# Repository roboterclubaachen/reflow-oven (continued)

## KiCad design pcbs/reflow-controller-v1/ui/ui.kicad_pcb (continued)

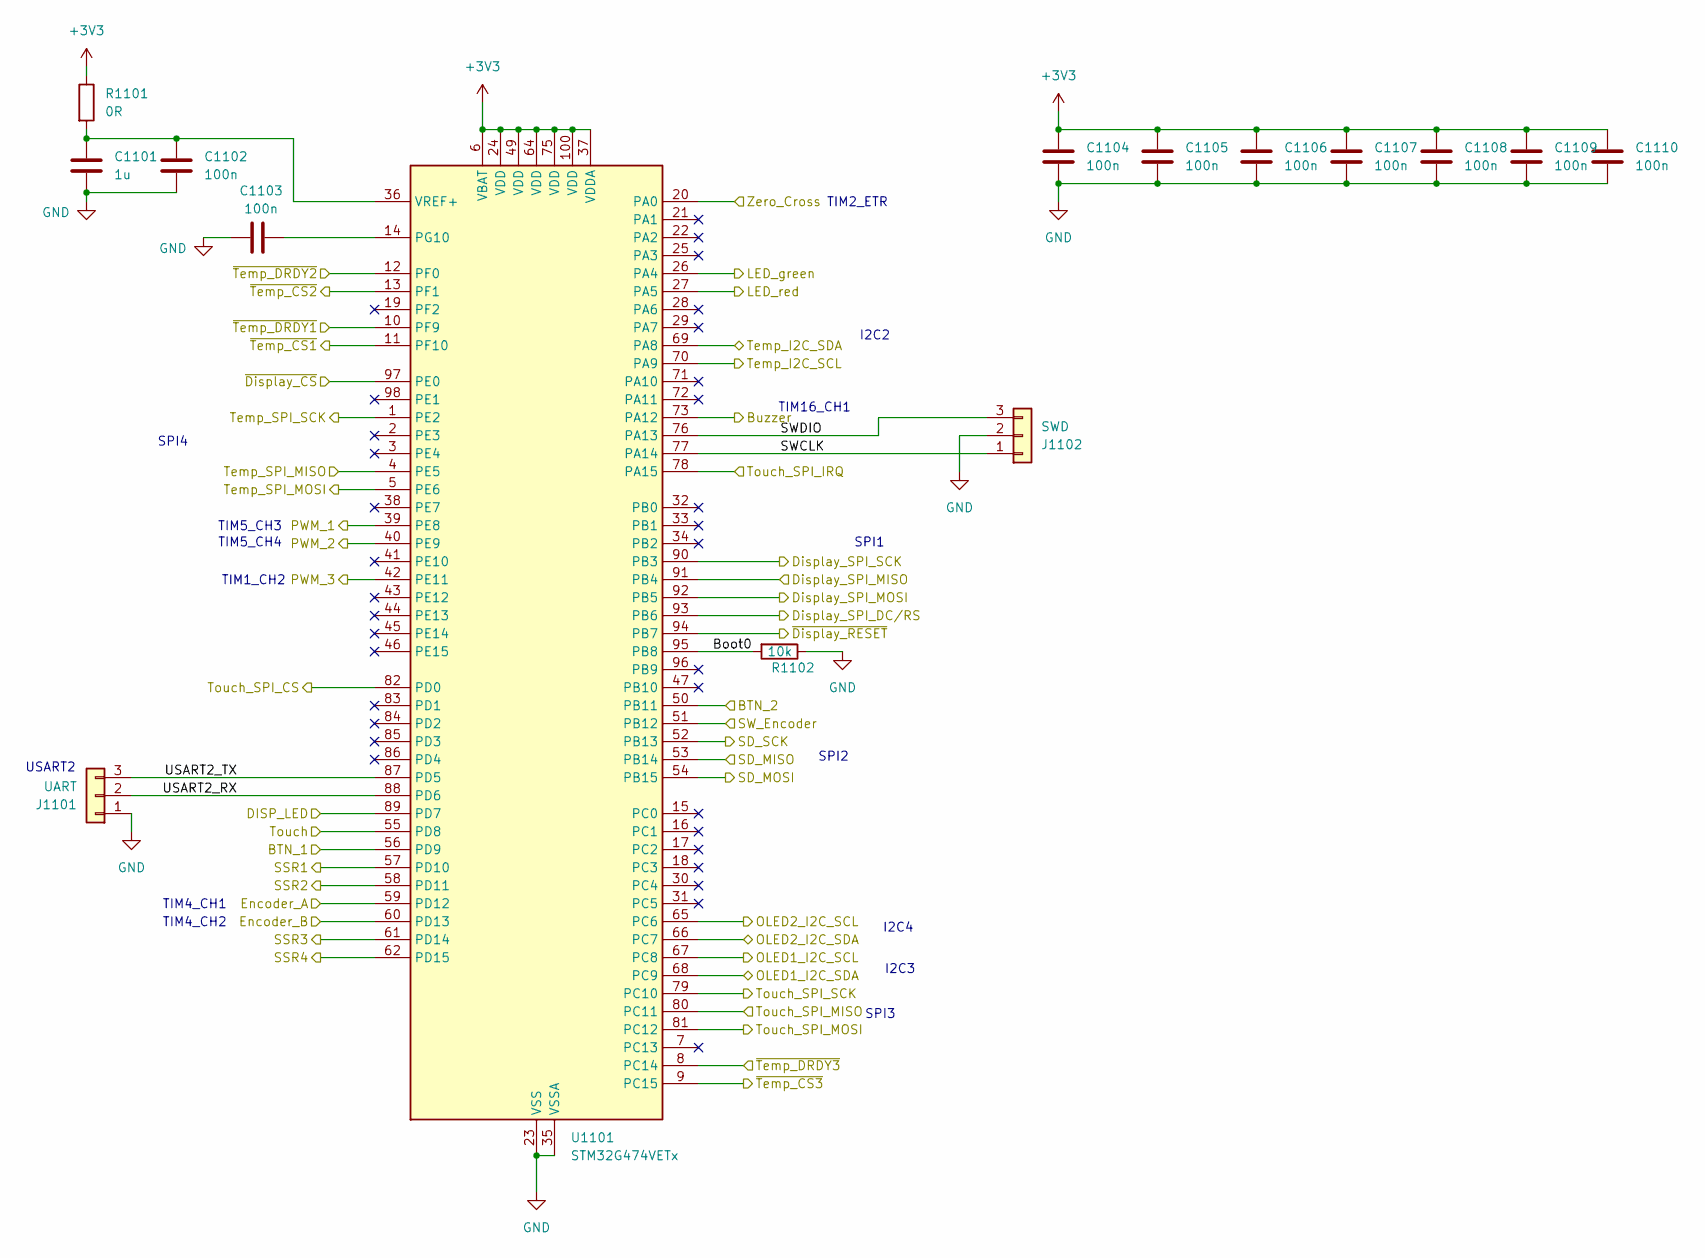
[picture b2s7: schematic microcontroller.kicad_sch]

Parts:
C1101: 1u; C_0603_1608Metric
C1102, C1103, C1104, C1105, C1106, C1107, C1108, C1109, C1110: 100n; C_0603_1608Metric
J1101: UART; Molex_KK-254_AE-6410-03A_1x03_P2.54mm_Vertical
J1102: SWD; Molex_KK-254_AE-6410-03A_1x03_P2.54mm_Vertical
R1101: 0R; R_0603_1608Metric
R1102: 10k; R_0603_1608Metric
U1101: STM32G474VETx; LQFP-100_14x14mm_P0.5mm

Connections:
+3V3: C1104.1, C1105.1, C1106.1, C1107.1, C1108.1, C1109.1, C1110.1, R1101.1, U1101.6 (VBAT), U1101.24 (VDD), U1101.37 (VDDA), U1101.49 (VDD), U1101.64 (VDD), U1101.75 (VDD), U1101.100 (VDD); also elsewhere on the board
/Buttons/Buzzer: U1101.73 (PA12); also elsewhere on the board
/Buttons/Encoder_A: U1101.59 (PD12); also elsewhere on the board
/Buttons/Encoder_B: U1101.60 (PD13); also elsewhere on the board
/Buttons/LED_green: U1101.26 (PA4); also elsewhere on the board
/Buttons/LED_red: U1101.27 (PA5); also elsewhere on the board
/Buttons/SW_1: U1101.56 (PD9); also elsewhere on the board
/Buttons/SW_2: U1101.50 (PB11); also elsewhere on the board
/Buttons/SW_Encoder: U1101.51 (PB12); also elsewhere on the board
/Display LCD/DC/RS: U1101.93 (PB6); also elsewhere on the board
/Display LCD/LED: U1101.89 (PD7); also elsewhere on the board
/Display LCD/MISO: U1101.91 (PB4); also elsewhere on the board
/Display LCD/MOSI: U1101.92 (PB5); also elsewhere on the board
/Display LCD/SCK: U1101.90 (PB3); also elsewhere on the board
/Display LCD/SD_MISO: U1101.53 (PB14); also elsewhere on the board
/Display LCD/SD_MOSI: U1101.54 (PB15); also elsewhere on the board
/Display LCD/SD_SCK: U1101.52 (PB13); also elsewhere on the board
/Display LCD/T_CLK: U1101.79 (PC10); also elsewhere on the board
/Display LCD/T_CS: U1101.82 (PD0); also elsewhere on the board
/Display LCD/T_DIN: U1101.81 (PC12); also elsewhere on the board
/Display LCD/T_DO: U1101.80 (PC11); also elsewhere on the board
/Display LCD/T_IRQ: U1101.78 (PA15); also elsewhere on the board
/Display LCD/Touch: U1101.55 (PD8); also elsewhere on the board
/Display LCD/~CS: U1101.97 (PE0); also elsewhere on the board
/Display LCD/~RESET: U1101.94 (PB7); also elsewhere on the board
/Display OLED 1/I2C_SCL: U1101.67 (PC8); also elsewhere on the board
/Display OLED 1/I2C_SDA: U1101.68 (PC9); also elsewhere on the board
/Display OLED 2/I2C_SCL: U1101.65 (PC6); also elsewhere on the board
/Display OLED 2/I2C_SDA: U1101.66 (PC7); also elsewhere on the board
/Fan_PWM: U1101.42 (PE11); also elsewhere on the board
/PCB Interconnect/SSR1: U1101.57 (PD10); also elsewhere on the board
/PCB Interconnect/SSR2: U1101.58 (PD11); also elsewhere on the board
/PCB Interconnect/SSR3: U1101.62 (PD15); also elsewhere on the board
/PCB Interconnect/SSR4: U1101.61 (PD14); also elsewhere on the board
/PCB Interconnect/Zero: U1101.20 (PA0); also elsewhere on the board
/Servo1: U1101.39 (PE8); also elsewhere on the board
/Servo2: U1101.40 (PE9); also elsewhere on the board
/Temperature onboard 1/SCL: U1101.70 (PA9); also elsewhere on the board
/Temperature onboard 1/SDA: U1101.69 (PA8); also elsewhere on the board
/Temperature sensor 1/SCLK: U1101.1 (PE2); also elsewhere on the board
/Temperature sensor 1/SDI: U1101.5 (PE6); also elsewhere on the board
/Temperature sensor 1/SDO: U1101.4 (PE5); also elsewhere on the board
/Temperature sensor 1/~CS: U1101.9 (PC15); also elsewhere on the board
/Temperature sensor 1/~DRDY: U1101.8 (PC14); also elsewhere on the board
/Temperature sensor 2/~CS: U1101.11 (PF10); also elsewhere on the board
/Temperature sensor 2/~DRDY: U1101.10 (PF9); also elsewhere on the board
/Temperature sensor 3/~CS: U1101.13 (PF1); also elsewhere on the board
/Temperature sensor 3/~DRDY: U1101.12 (PF0); also elsewhere on the board
/microcontroller/Boot0: R1102.2, U1101.95 (PB8)
/microcontroller/SWCLK: J1102.1, U1101.77 (PA14)
/microcontroller/SWDIO: J1102.3, U1101.76 (PA13)
/microcontroller/USART2_RX: J1101.2, U1101.88 (PD6)
/microcontroller/USART2_TX: J1101.3, U1101.87 (PD5)
unnamed: C1103.2, U1101.14 (PG10)
unnamed: C1101.1, C1102.1, R1101.2, U1101.36 (VREF+)

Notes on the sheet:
SPI4
TIM2_ETR
TIM5_CH3
TIM4_CH2
SPI3
I2C4
I2C2
SPI2
TIM16_CH1
TIM4_CH1
SPI1
I2C3
USART2
TIM5_CH4
TIM1_CH2

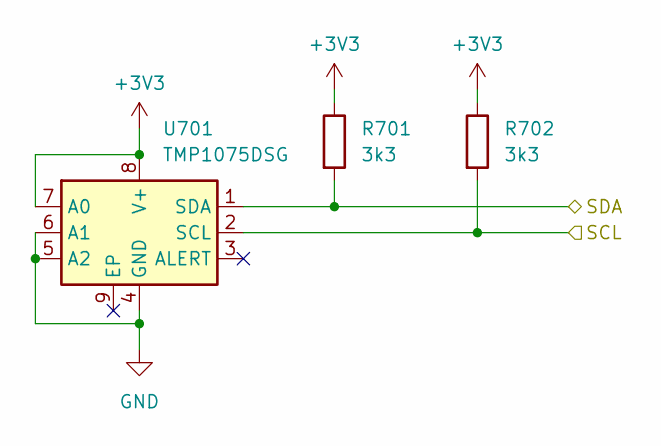
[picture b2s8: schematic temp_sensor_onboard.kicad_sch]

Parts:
R701, R702: 3k3; R_0603_1608Metric
U701: TMP1075DSG; WSON-8-1EP_2x2mm_P0.5mm_EP0.9x1.6mm_ThermalVias

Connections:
+3V3: R701.1, R702.1, U701.7 (A0), U701.8 (V+); also elsewhere on the board
/Temperature onboard 1/SCL: R702.2, U701.2 (SCL); also elsewhere on the board
/Temperature onboard 1/SDA: R701.2, U701.1 (SDA); also elsewhere on the board

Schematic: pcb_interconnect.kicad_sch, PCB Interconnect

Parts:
J801: Power; JST_XH_B3B-XH-A_1x03_P2.50mm_Vertical
J802: Data; JST_GH_BM05B-GHS-TBT_1x05-1MP_P1.25mm_Vertical

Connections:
/Temperature sensor 1/FORCE+: J801.1; also elsewhere on the board
/Temperature sensor 1/RTDIN+: J801.2; also elsewhere on the board

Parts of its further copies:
J201: Power; JST_XH_B3B-XH-A_1x03_P2.50mm_Vertical
J202: Data; JST_GH_BM05B-GHS-TBT_1x05-1MP_P1.25mm_Vertical

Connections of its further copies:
+3.3V: J201.2
+5V: J201.1; also elsewhere on the board
/PCB Interconnect/SSR1: J202.1; also elsewhere on the board
/PCB Interconnect/SSR2: J202.2; also elsewhere on the board
/PCB Interconnect/SSR3: J202.3; also elsewhere on the board
/PCB Interconnect/SSR4: J202.4; also elsewhere on the board
/PCB Interconnect/Zero: J202.5; also elsewhere on the board

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
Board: 2 copper layers, 92 parts (0 on the bottom side), 92 nets, no tracks yet.

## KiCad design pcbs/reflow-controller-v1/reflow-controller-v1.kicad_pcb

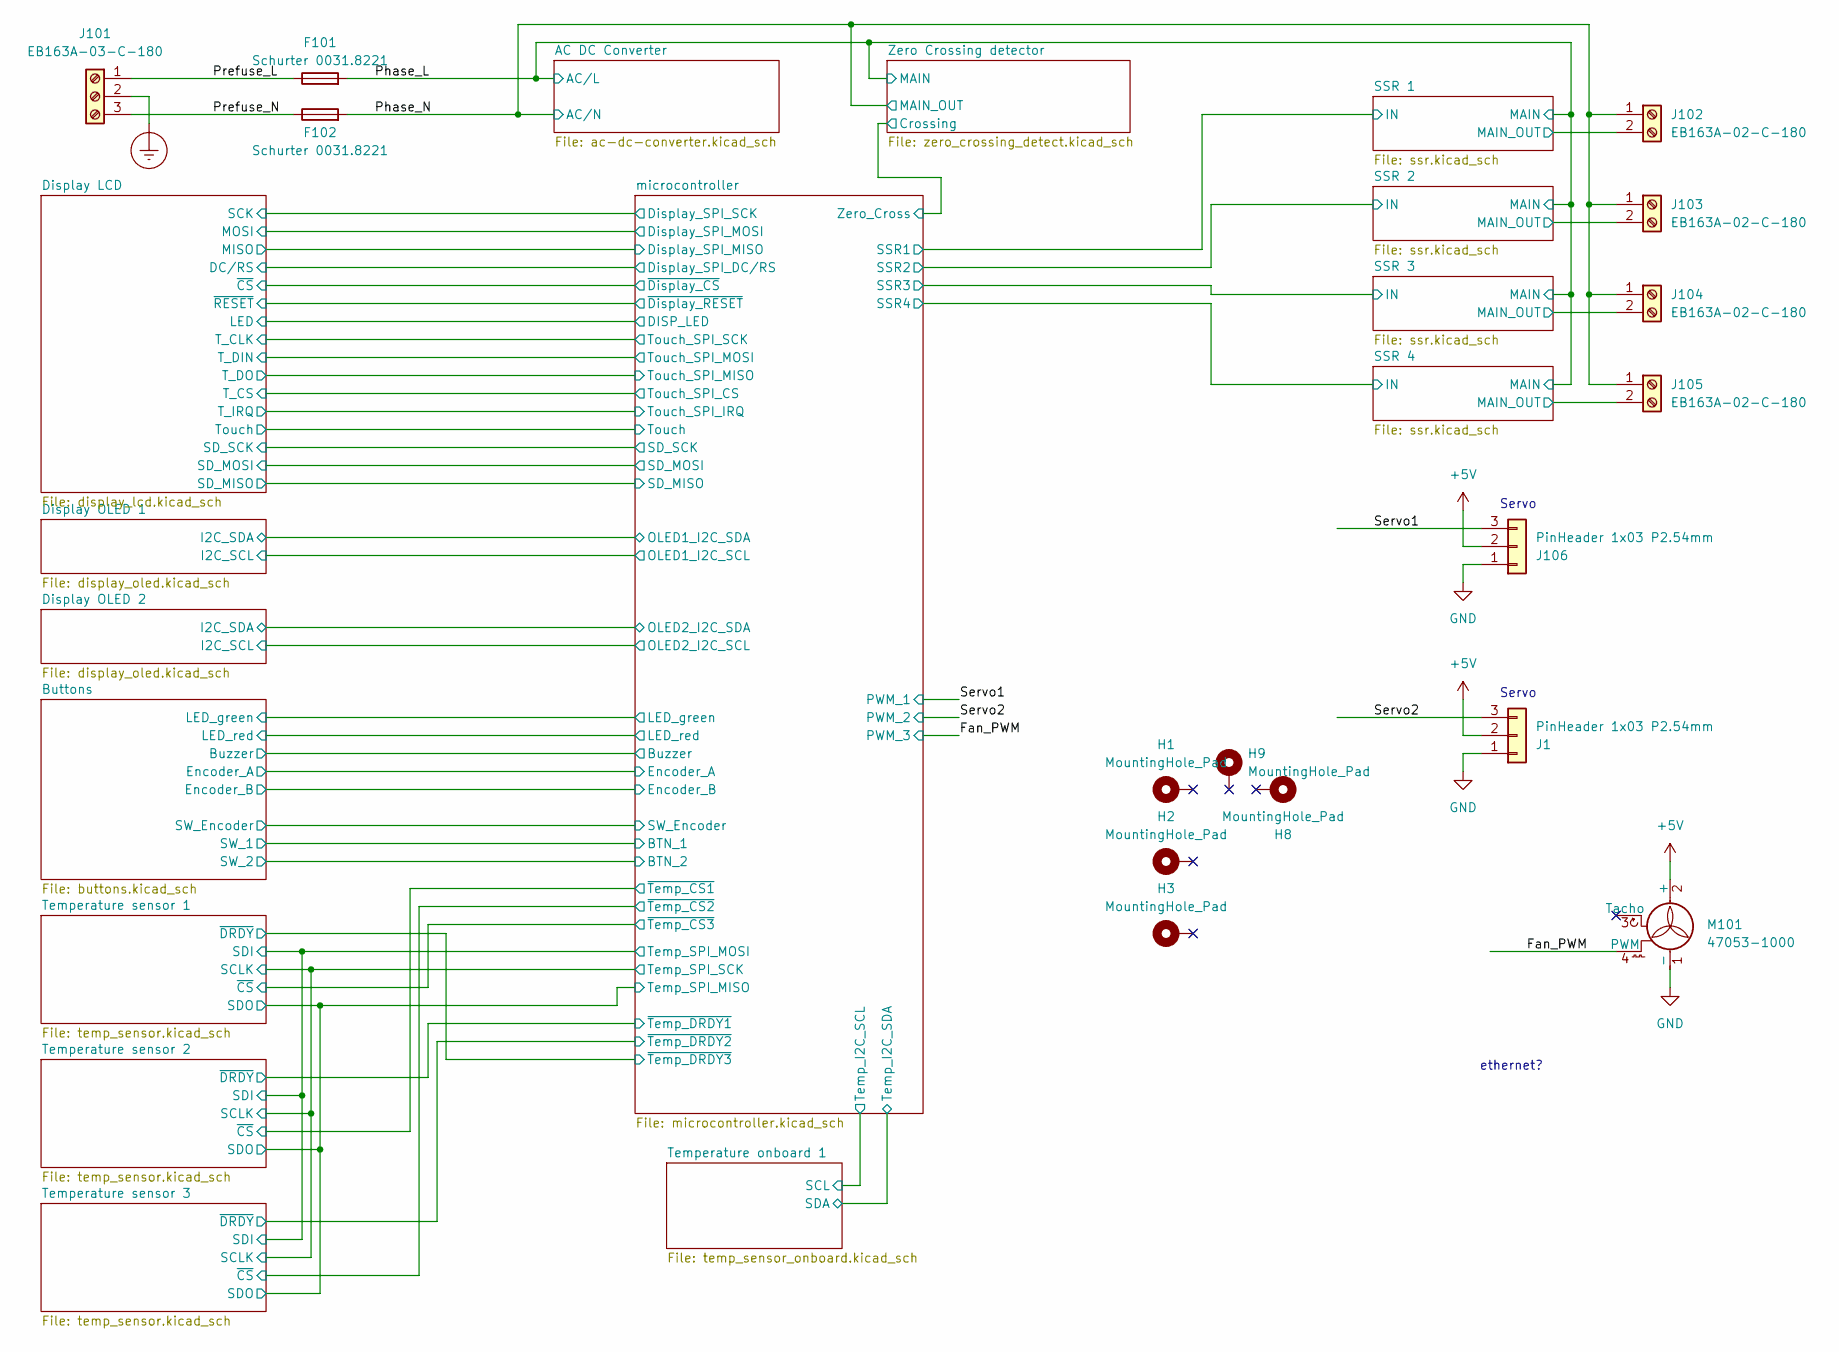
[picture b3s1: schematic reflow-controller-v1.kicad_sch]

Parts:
F101, F102: Schurter 0031.8221; Fuseholder_Cylinder-5x20mm_Schurter_OGN-SMD_Horizontal_Open
H1, H2, H3, H8, H9: MountingHole_Pad; Mounting_Wuerth_WA-SMSI-M3_H15mm_9774150360
J1, J106: PinHeader 1x03 P2.54mm; PinHeader_1x03_P2.54mm_Vertical
J101: EB163A-03-C-180; PhoenixContact_SPT_2.5_3-V-5.0-EX_1x03_P5.0mm_Vertical
J102, J103, J104, J105: EB163A-02-C-180; PhoenixContact_SPT_2.5_2-V-5.0-EX_1x02_P5.0mm_Vertical
M101: 47053-1000; Molex_KK-254_AE-6410-04A_1x04_P2.54mm_Vertical

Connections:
+5V: J1.2, J106.2, M101.2 (+); also elsewhere on the board
/Fan_PWM: M101.4 (PWM); also elsewhere on the board
/Phase_L: F101.2; also elsewhere on the board
/Phase_N: F102.2, J102.1, J103.1, J104.1, J105.1; also elsewhere on the board
/Prefuse_L: F101.1, J101.1
/Prefuse_N: F102.1, J101.3
/SSR 1/MAIN_OUT: J102.2; also elsewhere on the board
/SSR 2/MAIN_OUT: J103.2; also elsewhere on the board
/SSR 3/MAIN_OUT: J104.2; also elsewhere on the board
/SSR 4/MAIN_OUT: J105.2; also elsewhere on the board
/Servo1: J106.3; also elsewhere on the board
/Servo2: J1.3; also elsewhere on the board
Earth_Protective: J101.2
GND: J1.1, J106.1, M101.1 (-); also elsewhere on the board

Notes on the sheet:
Servo
ethernet?

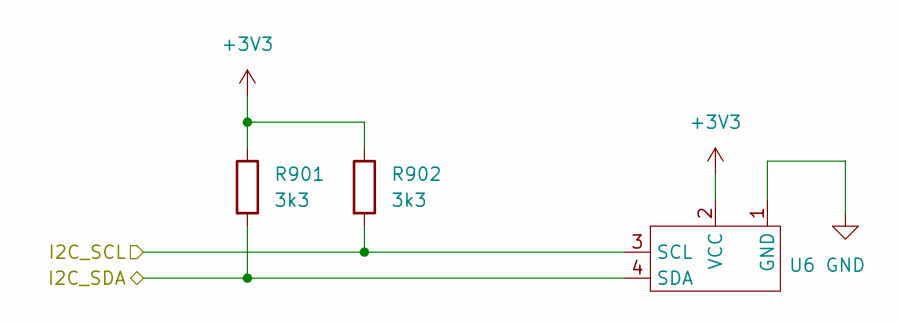
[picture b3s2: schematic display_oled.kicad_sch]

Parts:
R901, R902: 3k3; R_0603_1608Metric
U6: SSD1315 Module

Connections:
+3V3: R901.1, R902.1, U6.2 (VCC); also elsewhere on the board
/Display OLED 2/I2C_SCL: R902.2, U6.3 (SCL); also elsewhere on the board
/Display OLED 2/I2C_SDA: R901.2, U6.4 (SDA); also elsewhere on the board
GND: U6.1 (GND); also elsewhere on the board

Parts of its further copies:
R801, R802: 3k3; R_0603_1608Metric
U5: SSD1315 Module

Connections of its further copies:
+3V3: R801.1, R802.1, U5.2 (VCC); also elsewhere on the board
/Display OLED 1/I2C_SCL: R802.2, U5.3 (SCL); also elsewhere on the board
/Display OLED 1/I2C_SDA: R801.2, U5.4 (SDA); also elsewhere on the board
GND: U5.1 (GND); also elsewhere on the board

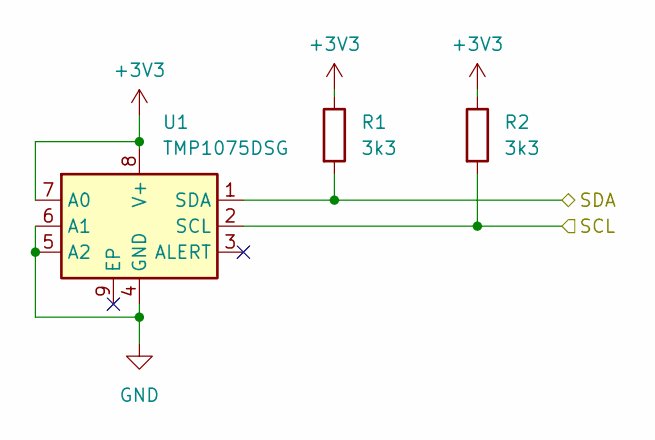
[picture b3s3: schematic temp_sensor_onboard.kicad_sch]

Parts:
R1, R2: 3k3; R_0603_1608Metric
U1: TMP1075DSG; WSON-8-1EP_2x2mm_P0.5mm_EP0.9x1.6mm_ThermalVias

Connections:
+3V3: R1.1, R2.1, U1.7 (A0), U1.8 (V+); also elsewhere on the board
/Temperature onboard 1/SCL: R2.2, U1.2 (SCL); also elsewhere on the board
/Temperature onboard 1/SDA: R1.2, U1.1 (SDA); also elsewhere on the board
GND: U1.4 (GND), U1.5 (A2), U1.6 (A1); also elsewhere on the board

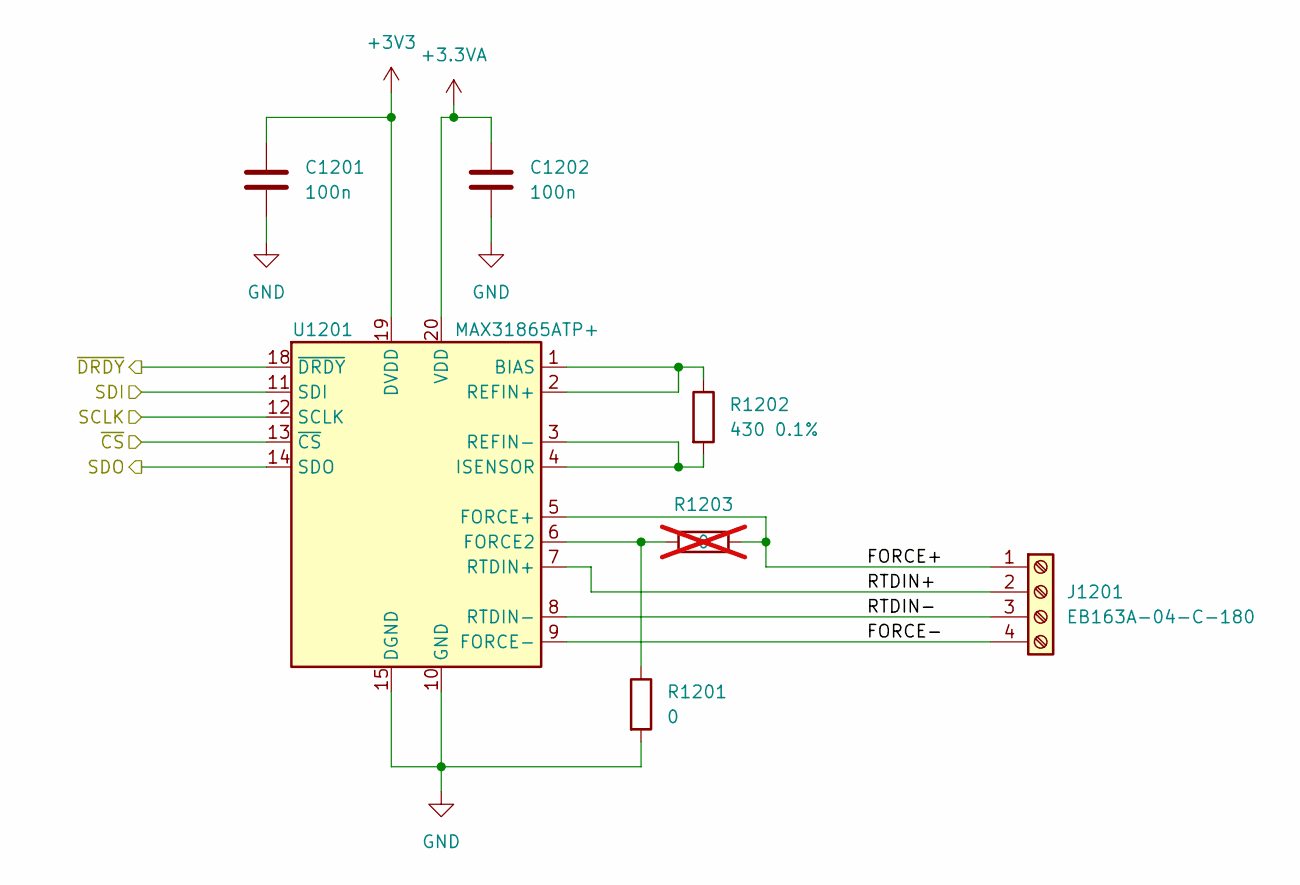
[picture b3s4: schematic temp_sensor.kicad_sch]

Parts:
C1201, C1202: 100n; C_0603_1608Metric
J1201: EB163A-04-C-180; PhoenixContact_SPT_2.5_4-V-5.0-EX_1x04_P5.0mm_Vertical
R1201: 0; R_0603_1608Metric
R1202: 430 0.1%; R_1206_3216Metric
R1203: 0; R_0603_1608Metric; not fitted
U1201: MAX31865ATP+; TQFN-20-1EP_5x5mm_P0.65mm_EP3.25x3.25mm

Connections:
+3.3VA: C1202.1, U1201.20 (VDD); also elsewhere on the board
+3V3: C1201.1, U1201.19 (DVDD); also elsewhere on the board
/Temperature sensor 1/SCLK: U1201.12 (SCLK); also elsewhere on the board
/Temperature sensor 1/SDI: U1201.11 (SDI); also elsewhere on the board
/Temperature sensor 1/SDO: U1201.14 (SDO); also elsewhere on the board
/Temperature sensor 2/FORCE+: J1201.1, R1203.2, U1201.5 (FORCE+)
/Temperature sensor 2/FORCE-: J1201.4, U1201.9 (FORCE-)
/Temperature sensor 2/RTDIN+: J1201.2, U1201.7 (RTDIN+)
/Temperature sensor 2/RTDIN-: J1201.3, U1201.8 (RTDIN-)
/Temperature sensor 2/~CS: U1201.13 (~CS); also elsewhere on the board
/Temperature sensor 2/~DRDY: U1201.18 (~DRDY); also elsewhere on the board
GND: C1201.2, C1202.2, R1201.2, U1201.10 (GND), U1201.15 (DGND), U1201.16 (GND), U1201.21 (GND); also elsewhere on the board
unnamed: R1202.1, U1201.1 (BIAS), U1201.2 (REFIN+)
unnamed: R1201.1, R1203.1, U1201.6 (FORCE2)
unnamed: R1202.2, U1201.3 (REFIN-), U1201.4 (ISENSOR)

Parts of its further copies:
C1101, C1102, C1301, C1302: 100n; C_0603_1608Metric
J1101, J1301: EB163A-04-C-180; PhoenixContact_SPT_2.5_4-V-5.0-EX_1x04_P5.0mm_Vertical
R1101, R1302: 430 0.1%; R_1206_3216Metric
R1102, R1301: 0; R_0603_1608Metric
R1103, R1303: 0; R_0603_1608Metric; not fitted
U1101, U1301: MAX31865ATP+; TQFN-20-1EP_5x5mm_P0.65mm_EP3.25x3.25mm

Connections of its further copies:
+3.3VA: C1101.1, C1302.1, U1101.20 (VDD), U1301.20 (VDD); also elsewhere on the board
+3V3: C1102.1, C1301.1, U1101.19 (DVDD), U1301.19 (DVDD); also elsewhere on the board
/Temperature sensor 1/FORCE+: J1101.1, R1103.2, U1101.5 (FORCE+)
/Temperature sensor 1/FORCE-: J1101.4, U1101.9 (FORCE-)
/Temperature sensor 1/RTDIN+: J1101.2, U1101.7 (RTDIN+)
/Temperature sensor 1/RTDIN-: J1101.3, U1101.8 (RTDIN-)
/Temperature sensor 1/SCLK: U1101.12 (SCLK), U1301.12 (SCLK); also elsewhere on the board
/Temperature sensor 1/SDI: U1101.11 (SDI), U1301.11 (SDI); also elsewhere on the board
/Temperature sensor 1/SDO: U1101.14 (SDO), U1301.14 (SDO); also elsewhere on the board
/Temperature sensor 1/~CS: U1101.13 (~CS); also elsewhere on the board
/Temperature sensor 1/~DRDY: U1101.18 (~DRDY); also elsewhere on the board
/Temperature sensor 3/FORCE+: J1301.1, R1303.2, U1301.5 (FORCE+)
/Temperature sensor 3/FORCE-: J1301.4, U1301.9 (FORCE-)
/Temperature sensor 3/RTDIN+: J1301.2, U1301.7 (RTDIN+)
/Temperature sensor 3/RTDIN-: J1301.3, U1301.8 (RTDIN-)
/Temperature sensor 3/~CS: U1301.13 (~CS); also elsewhere on the board
/Temperature sensor 3/~DRDY: U1301.18 (~DRDY); also elsewhere on the board
GND: C1101.2, C1102.2, C1301.2, C1302.2, R1102.2, R1301.2, U1101.10 (GND), U1101.15 (DGND), U1101.16 (GND), U1101.21 (GND), U1301.10 (GND), U1301.15 (DGND), U1301.16 (GND), U1301.21 (GND); also elsewhere on the board
unnamed: R1101.1, U1101.1 (BIAS), U1101.2 (REFIN+)
unnamed: R1102.1, R1103.1, U1101.6 (FORCE2)
unnamed: R1101.2, U1101.3 (REFIN-), U1101.4 (ISENSOR)
unnamed: R1302.1, U1301.1 (BIAS), U1301.2 (REFIN+)
unnamed: R1301.1, R1303.1, U1301.6 (FORCE2)
unnamed: R1302.2, U1301.3 (REFIN-), U1301.4 (ISENSOR)

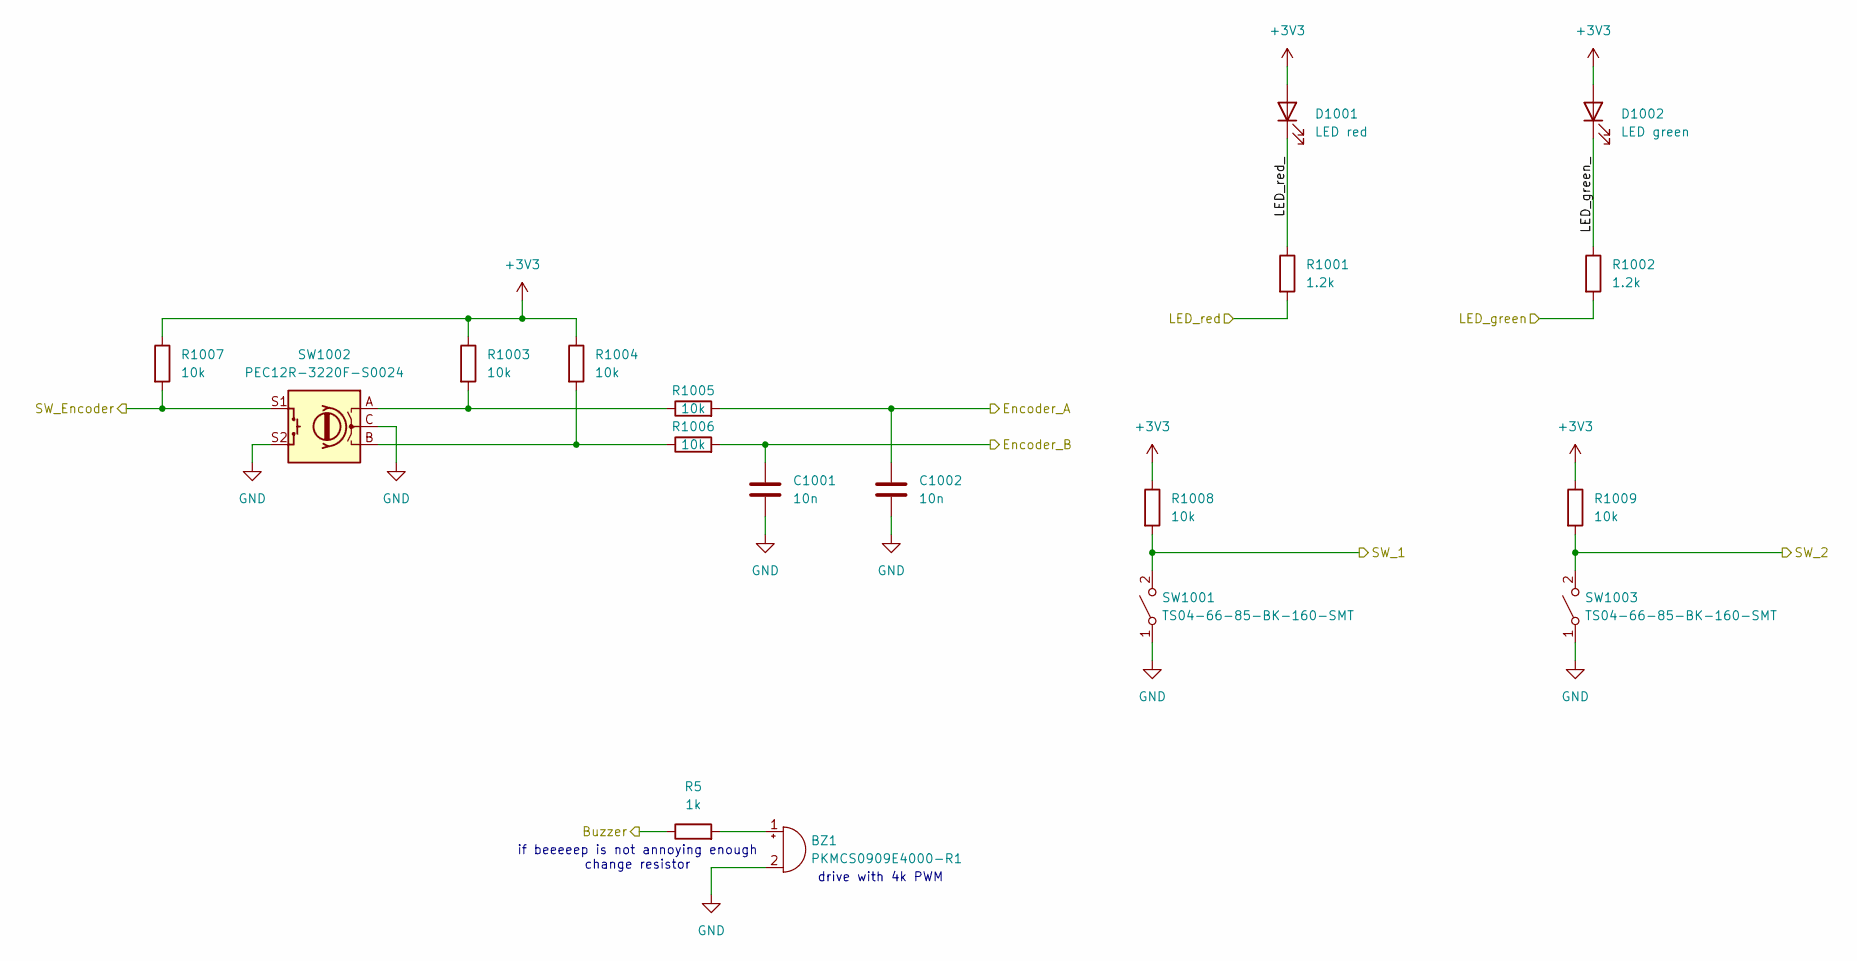
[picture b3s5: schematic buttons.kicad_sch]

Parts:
BZ1: PKMCS0909E4000-R1; Buzzer_Murata_PKMCS0909E
C1001, C1002: 10n; C_0603_1608Metric
D1001: LED red; LED_0603_1608Metric
D1002: LED green; LED_0603_1608Metric
R5: 1k; R_0603_1608Metric
R1001, R1002: 1.2k; R_0603_1608Metric
R1003, R1004, R1005, R1006, R1007, R1008, R1009: 10k; R_0603_1608Metric
SW1001, SW1003: TS04-66-85-BK-160-SMT; SW_Push_1P1T_NO_6x6mm_H9.5mm
SW1002: PEC12R-3220F-S0024; RotaryEncoder_Bourns_Vertical_PEC12R-3x17F-Sxxxx

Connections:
+3V3: D1001.2 (A), D1002.2 (A), R1003.1, R1004.1, R1007.1, R1008.1, R1009.1; also elsewhere on the board
/Buttons/Buzzer: R5.1; also elsewhere on the board
/Buttons/Encoder_A: C1002.1, R1005.2; also elsewhere on the board
/Buttons/Encoder_B: C1001.1, R1006.2; also elsewhere on the board
/Buttons/LED_green: R1002.2; also elsewhere on the board
/Buttons/LED_green_: D1002.1 (K), R1002.1
/Buttons/LED_red: R1001.2; also elsewhere on the board
/Buttons/LED_red_: D1001.1 (K), R1001.1
/Buttons/SW_1: R1008.2, SW1001.2 (B); also elsewhere on the board
/Buttons/SW_2: R1009.2, SW1003.2 (B); also elsewhere on the board
/Buttons/SW_Encoder: R1007.2, SW1002.S1; also elsewhere on the board
GND: BZ1.2 (-), C1001.2, C1002.2, SW1001.1 (A), SW1002.C, SW1002.S2, SW1003.1 (A); also elsewhere on the board
unnamed: BZ1.1 (+), R5.2
unnamed: R1003.2, R1005.1, SW1002.A
unnamed: R1004.2, R1006.1, SW1002.B

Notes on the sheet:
if beeeeep is not annoying enough change resistor
drive with 4k PWM

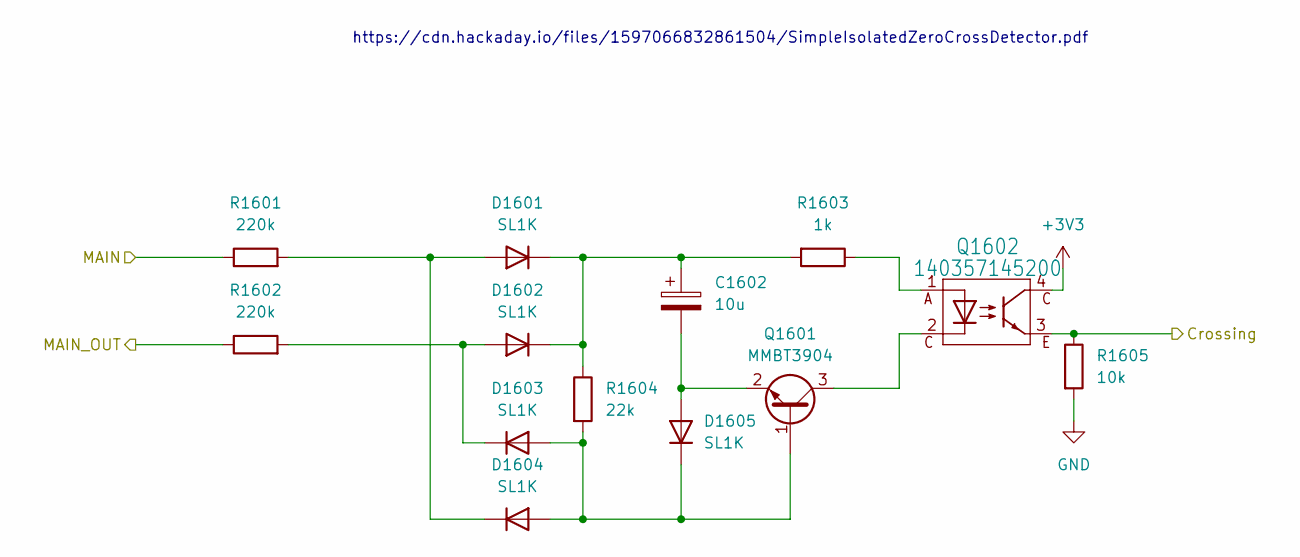
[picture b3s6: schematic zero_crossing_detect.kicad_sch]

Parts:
C1602: 10u; CP_Elec_4x5.7
D1601, D1602, D1603, D1604, D1605: SL1K; D_SOD-123F
Q1601: MMBT3904; SOT-23
Q1602: 140357145200; WL-OCPT_LSOP4
R1601, R1602: 220k; R_1206_3216Metric
R1603: 1k; R_0603_1608Metric
R1604: 22k; R_0603_1608Metric
R1605: 10k; R_0603_1608Metric

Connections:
+3V3: Q1602.4; also elsewhere on the board
/Phase_L: R1601.1; also elsewhere on the board
/Phase_N: R1602.1; also elsewhere on the board
/Zero Crossing detector/Crossing: Q1602.3, R1605.1; also elsewhere on the board
GND: R1605.2; also elsewhere on the board
unnamed: D1601.2 (A), D1604.1 (K), R1601.2
unnamed: C1602.1, D1601.1 (K), D1602.1 (K), R1603.2, R1604.1
unnamed: D1602.2 (A), D1603.1 (K), R1602.2
unnamed: D1603.2 (A), D1604.2 (A), D1605.1 (K), Q1601.1 (B), R1604.2
unnamed: C1602.2, D1605.2 (A), Q1601.2 (E)
unnamed: Q1601.3 (C), Q1602.2
unnamed: Q1602.1, R1603.1

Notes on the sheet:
https://cdn.hackaday.io/files/1597066832861504/SimpleIsolatedZeroCrossDetector.pdf

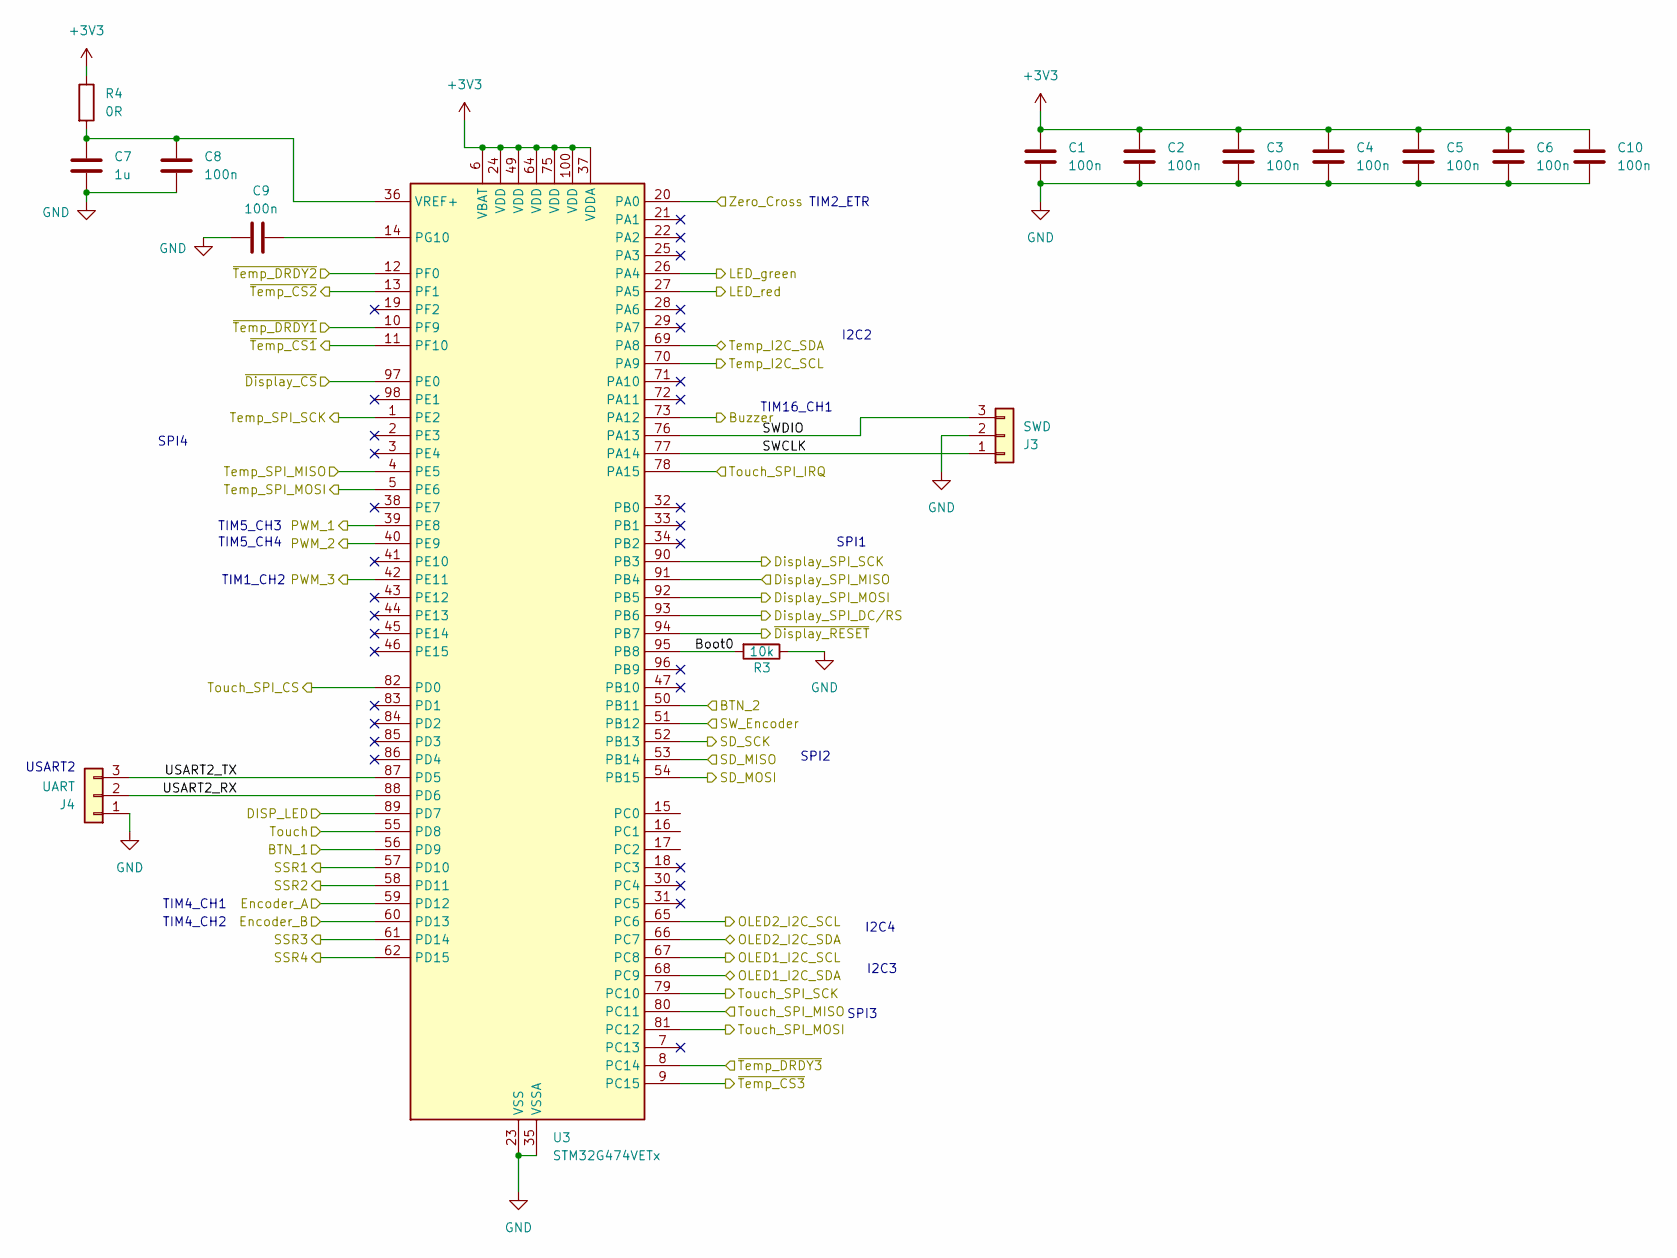
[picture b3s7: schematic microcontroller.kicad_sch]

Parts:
C1, C2, C3, C4, C5, C6, C8, C9, C10: 100n; C_0603_1608Metric
C7: 1u; C_0603_1608Metric
J3: SWD; Molex_KK-254_AE-6410-03A_1x03_P2.54mm_Vertical
J4: UART; Molex_KK-254_AE-6410-03A_1x03_P2.54mm_Vertical
R3: 10k; R_0603_1608Metric
R4: 0R; R_0603_1608Metric
U3: STM32G474VETx; LQFP-100_14x14mm_P0.5mm

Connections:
+3V3: C1.1, C2.1, C3.1, C4.1, C5.1, C6.1, C10.1, R4.1, U3.6 (VBAT), U3.24 (VDD), U3.37 (VDDA), U3.49 (VDD), U3.64 (VDD), U3.75 (VDD), U3.100 (VDD); also elsewhere on the board
/Buttons/Buzzer: U3.73 (PA12); also elsewhere on the board
/Buttons/Encoder_A: U3.59 (PD12); also elsewhere on the board
/Buttons/Encoder_B: U3.60 (PD13); also elsewhere on the board
/Buttons/LED_green: U3.26 (PA4); also elsewhere on the board
/Buttons/LED_red: U3.27 (PA5); also elsewhere on the board
/Buttons/SW_1: U3.56 (PD9); also elsewhere on the board
/Buttons/SW_2: U3.50 (PB11); also elsewhere on the board
/Buttons/SW_Encoder: U3.51 (PB12); also elsewhere on the board
/Display LCD/DC/RS: U3.93 (PB6); also elsewhere on the board
/Display LCD/LED: U3.89 (PD7); also elsewhere on the board
/Display LCD/MISO: U3.91 (PB4); also elsewhere on the board
/Display LCD/MOSI: U3.92 (PB5); also elsewhere on the board
/Display LCD/SCK: U3.90 (PB3); also elsewhere on the board
/Display LCD/SD_MISO: U3.53 (PB14); also elsewhere on the board
/Display LCD/SD_MOSI: U3.54 (PB15); also elsewhere on the board
/Display LCD/SD_SCK: U3.52 (PB13); also elsewhere on the board
/Display LCD/T_CLK: U3.79 (PC10); also elsewhere on the board
/Display LCD/T_CS: U3.82 (PD0); also elsewhere on the board
/Display LCD/T_DIN: U3.81 (PC12); also elsewhere on the board
/Display LCD/T_DO: U3.80 (PC11); also elsewhere on the board
/Display LCD/T_IRQ: U3.78 (PA15); also elsewhere on the board
/Display LCD/Touch: U3.55 (PD8); also elsewhere on the board
/Display LCD/~CS: U3.97 (PE0); also elsewhere on the board
/Display LCD/~RESET: U3.94 (PB7); also elsewhere on the board
/Display OLED 1/I2C_SCL: U3.67 (PC8); also elsewhere on the board
/Display OLED 1/I2C_SDA: U3.68 (PC9); also elsewhere on the board
/Display OLED 2/I2C_SCL: U3.65 (PC6); also elsewhere on the board
/Display OLED 2/I2C_SDA: U3.66 (PC7); also elsewhere on the board
/Fan_PWM: U3.42 (PE11); also elsewhere on the board
/SSR 1/IN: U3.57 (PD10); also elsewhere on the board
/SSR 2/IN: U3.58 (PD11); also elsewhere on the board
/SSR 3/IN: U3.61 (PD14); also elsewhere on the board
/SSR 4/IN: U3.62 (PD15); also elsewhere on the board
/Servo1: U3.39 (PE8); also elsewhere on the board
/Servo2: U3.40 (PE9); also elsewhere on the board
/Temperature onboard 1/SCL: U3.70 (PA9); also elsewhere on the board
/Temperature onboard 1/SDA: U3.69 (PA8); also elsewhere on the board
/Temperature sensor 1/SCLK: U3.1 (PE2); also elsewhere on the board
/Temperature sensor 1/SDI: U3.5 (PE6); also elsewhere on the board
/Temperature sensor 1/SDO: U3.4 (PE5); also elsewhere on the board
/Temperature sensor 1/~CS: U3.9 (PC15); also elsewhere on the board
/Temperature sensor 1/~DRDY: U3.8 (PC14); also elsewhere on the board
/Temperature sensor 2/~CS: U3.11 (PF10); also elsewhere on the board
/Temperature sensor 2/~DRDY: U3.10 (PF9); also elsewhere on the board
/Temperature sensor 3/~CS: U3.13 (PF1); also elsewhere on the board
/Temperature sensor 3/~DRDY: U3.12 (PF0); also elsewhere on the board
/Zero Crossing detector/Crossing: U3.20 (PA0); also elsewhere on the board
/microcontroller/Boot0: R3.2, U3.95 (PB8)
/microcontroller/SWCLK: J3.1, U3.77 (PA14)
/microcontroller/SWDIO: J3.3, U3.76 (PA13)
/microcontroller/USART2_RX: J4.2, U3.88 (PD6)
/microcontroller/USART2_TX: J4.3, U3.87 (PD5)
GND: C1.2, C2.2, C3.2, C4.2, C5.2, C6.2, C7.2, C8.2, C9.1, C10.2, J3.2, J4.1, R3.1, U3.23 (VSS), U3.35 (VSSA), U3.48 (VSS), U3.63 (VSS), U3.74 (VSS), U3.99 (VSS); also elsewhere on the board
unnamed: C9.2, U3.14 (PG10)
unnamed: C7.1, C8.1, R4.2, U3.36 (VREF+)

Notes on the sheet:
SPI4
TIM2_ETR
TIM5_CH3
TIM4_CH2
SPI3
I2C4
I2C2
SPI2
TIM16_CH1
TIM4_CH1
SPI1
I2C3
USART2
TIM5_CH4
TIM1_CH2
